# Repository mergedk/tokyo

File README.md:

High voltage power supply for tima2.

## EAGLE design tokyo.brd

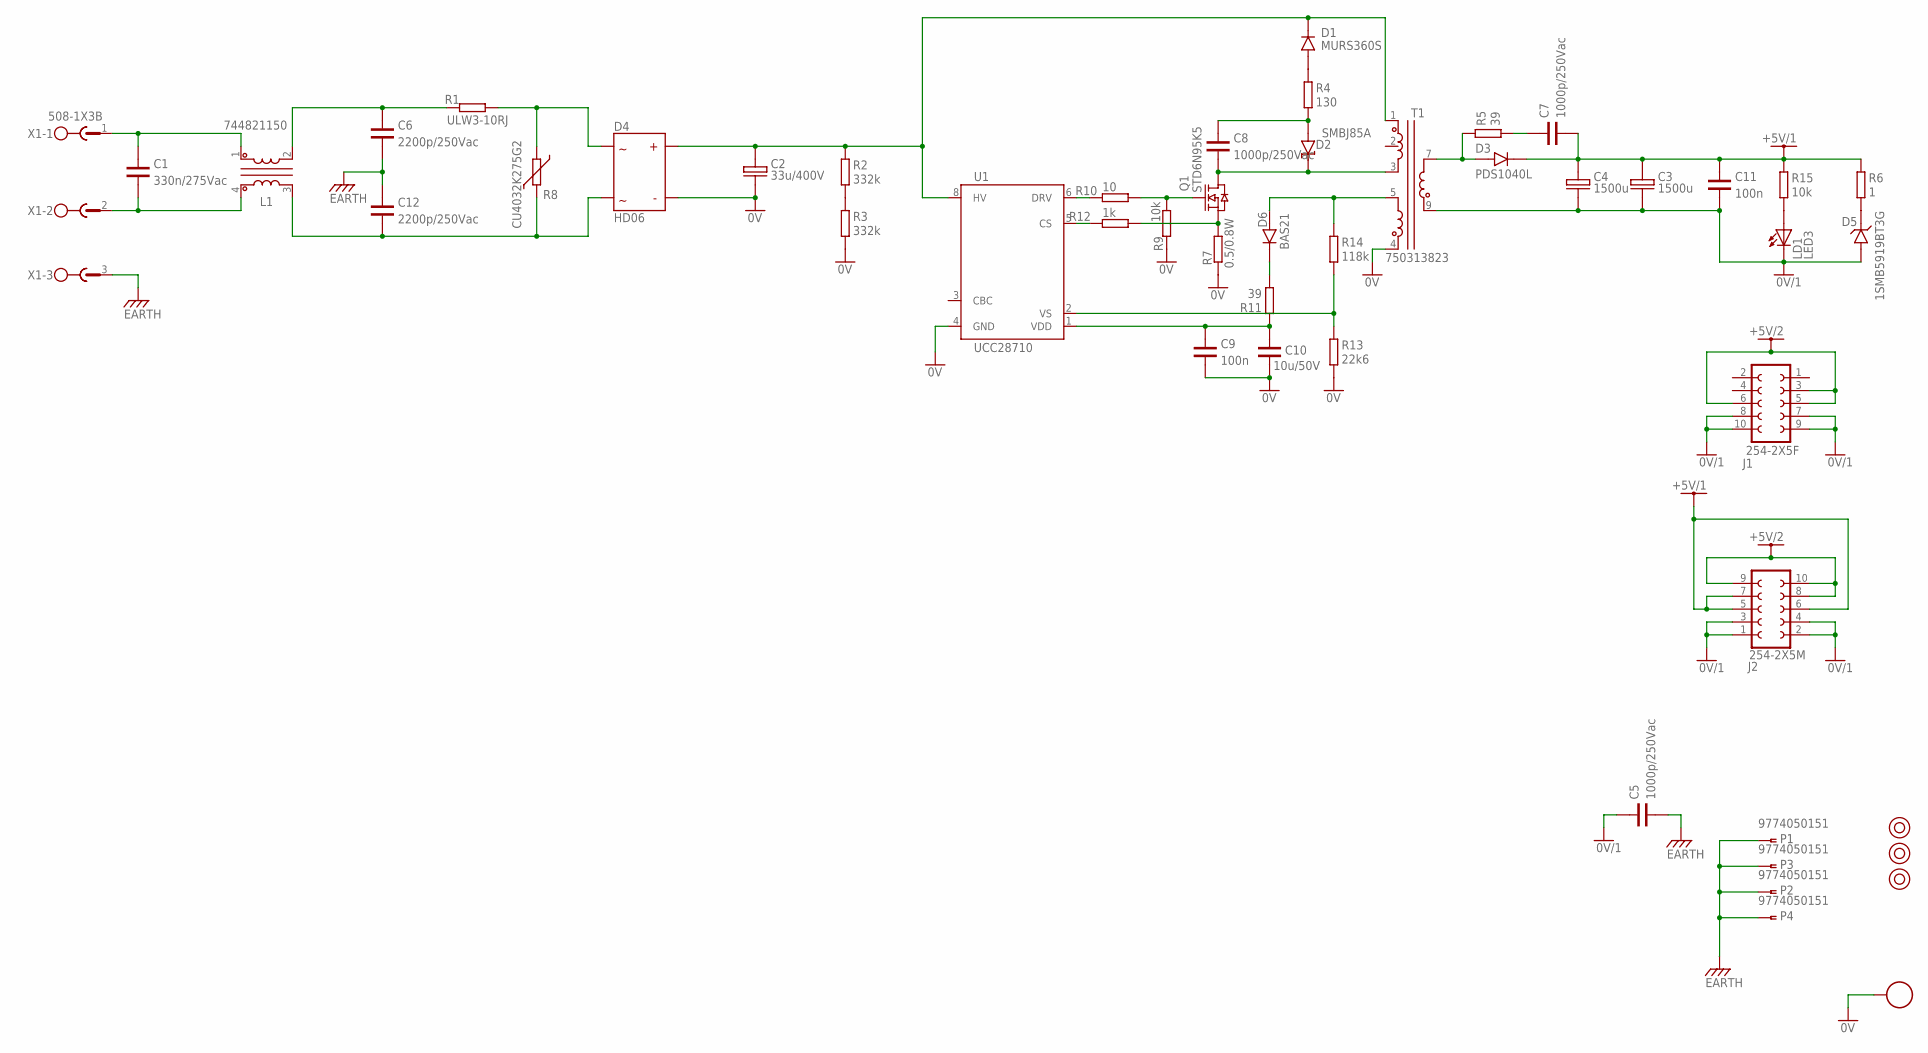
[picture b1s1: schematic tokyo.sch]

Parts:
0V: TESTPOINT
C1: 330n/275Vac; 15X8.5
C2: 33u/400V; D18
C3, C4: 1500u; D10
C5, C7, C8: 1000p/250Vac; 1812
C6, C12: 2200p/250Vac; 2211
C9, C11: 100n; 0603
C10: 10u/50V; 1206
D1: MURS360S; DO-214AA
D2: SMBJ85A; DO-214AA
D3: PDS1040L; POWERDI5
D4: HD06; MINIDIP
D5: 1SMB5919BT3G; DO-214AA
D6: BAS21; SOT23
FIDUCIAL1, FIDUCIAL2, FIDUCIAL3: FIDUCIAL
J1: 254-2X5F
J2: 254-2X5M
L1: 744821150
LD1: LED3
P1, P2, P3, P4: 9774050151
Q1: STD6N95K5; DPAK
R1: ULW3-10RJ; 15X6
R2, R3: 332k; 1206
R4: 130; 1206
R5: 39; 1206
R6: 1; 1206
R7: 0.5/0.8W; 2512
R8: CU4032K275G2; 4032
R9, R15: 10k; 0603
R10: 10; 0603
R11: 39; 0603
R12: 1k; 0603
R13: 22k6; 0603
R14: 118k; 0603
T1: 750313823; EE16
U1: UCC28710; SOIC7
X1: 508-1X3B

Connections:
0V: 0V.P$1, C2.2, C9.2, C10.2, D4.2, R3.2, R7.1, R9.1, R13.2, T1.4, U1.4 (GND)
0V/1: C3.2, C4.2, C5.1, C11.2, D5.2, J1.7, J1.8, J1.9, J1.10, J2.1, J2.2, J2.3, J2.4, LD1.C, T1.9
+5V/1: C3.1, C4.1, C7.2, C11.1, D3.3 (1), J2.5, J2.6, J2.7, R6.1, R15.1
+5V/2: J1.3, J1.5, J1.6, J2.8, J2.9, J2.10
EARTH: C5.2, C6.1 (2), C12.2 (1), P1.P1, P2.P1, P3.P1, P4.P1, X1.3
unnamed: C6.2 (1), L1.2, R1.1
unnamed: C12.1 (2), D4.4, L1.3, R8.2
unnamed: D6.1 (2), R14.1, T1.5
unnamed: D4.3, R1.P$2 (2), R8.1
unnamed: LD1.A, R15.2
unnamed: C7.1, R5.2
unnamed: R2.2, R3.1
unnamed: D3.1 (2), D3.2, R5.1, T1.7
unnamed: C2.1, D1.1, D4.1, R2.1, T1.1, U1.8 (HV)
unnamed: D1.2, R4.1
unnamed: C8.2, D2.1 (C), Q1.2 (D), T1.3
unnamed: Q1.3 (S), R7.2, R12.2
unnamed: R12.1, U1.5 (CS)
unnamed: Q1.1 (G), R9.2, R10.2
unnamed: C9.1, C10.1, R11.1, U1.1 (VDD)
unnamed: D5.1, R6.2
unnamed: C8.1, D2.2 (A), R4.2
unnamed: R13.1, R14.2, U1.2 (VS)
unnamed: C1.1, L1.1, X1.1
unnamed: C1.2, L1.4, X1.2
unnamed: R10.1, U1.6 (DRV)
unnamed: D6.3 (1), R11.2

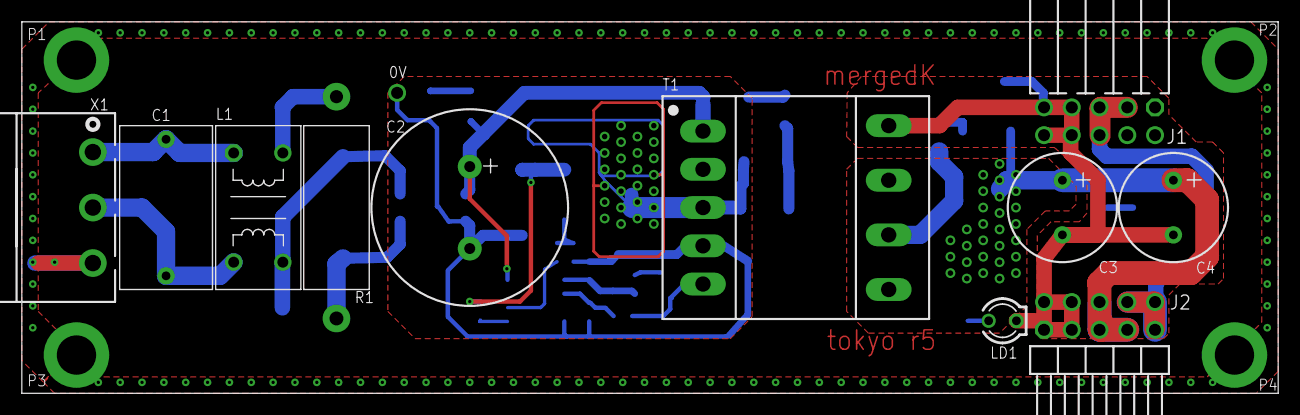
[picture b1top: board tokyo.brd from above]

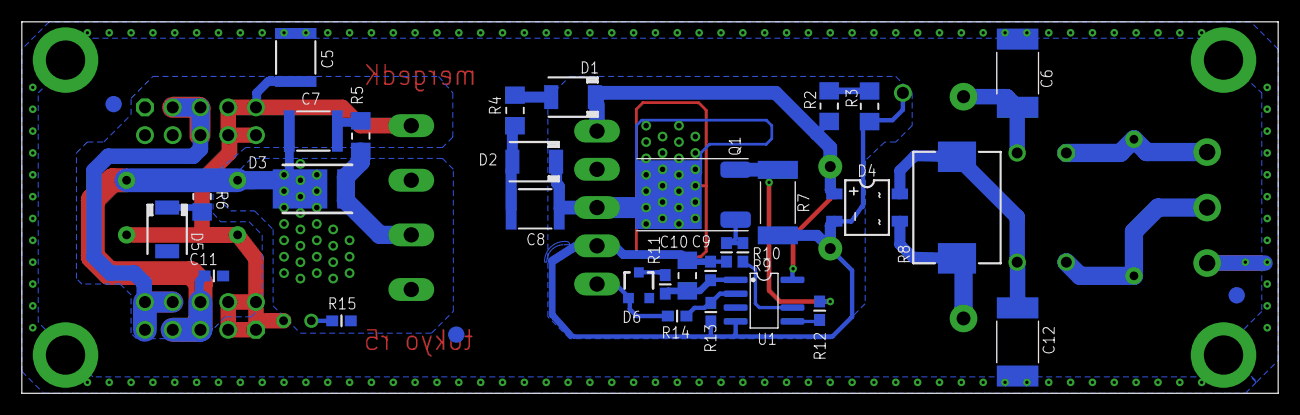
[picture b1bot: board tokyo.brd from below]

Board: 2 copper layers, 115.0 x 34.0 mm, 49 parts (33 on the bottom side), 27 nets.

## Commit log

2015-01-27 Initial commit.
2015-01-27 Added tag v1.2 for changeset fc9d06365303
2015-01-29 Ready for manufacture.
2015-01-29 Added tag v1.2 for changeset c222f043f248
2015-01-29 Updated libraries.
2015-01-29 Added tag v1.2 for changeset 9283e1c991b6
2015-02-19 Removed relais, added choke, added dissipation area for output diode, added minimum load circuiRemoved relais, added choke, added dissipation area for output diode, added minimum load circuit.
2015-03-02 Libraries updated.
2015-03-02 New placement of mounting holes.
2015-03-11 Revision for manufacturing.
2015-03-12 Updated libraries, added CONTENTS to repository.
2015-03-12 Added tag r3 for changeset 4e74b2b019d1
2015-03-27 Renamed CONTENTS, added TODO. Changed BOM format fron numbers to CSV.
2015-03-27 Corrected value for C10.
2015-06-14 Changed R3 to 330 (LD1 was too dim). Corrected BOM (LD1 should be a green LED).
2015-10-15 Incorporated changes required for EMC tests: replaced transzorb with varistor, changed position of line choke.
2015-10-19 Changed R15 to 10 k due to bright LED usage. Renumbered all components.
2015-10-19 Removed tokyo.bom from revision control.
2015-10-20 Changed values of R13 and R14 in order to get +5.5V on output.
2015-10-20 Added tag r4 for changeset e114fb834ed6
2017-11-26 Updated TODO (problems with redundant power supply operation).
2019-07-08 Added .hgignore to repo.
2019-07-08 Better .hgignore.
2019-07-08 Corrected +5V/2 routing.
2019-07-08 Added tag r5 for changeset effb2c5637cc
2019-08-25 Moved repo from mercurial to git.
2019-08-25 Removed leftover .hgignore.
2019-08-25 Add README.md
